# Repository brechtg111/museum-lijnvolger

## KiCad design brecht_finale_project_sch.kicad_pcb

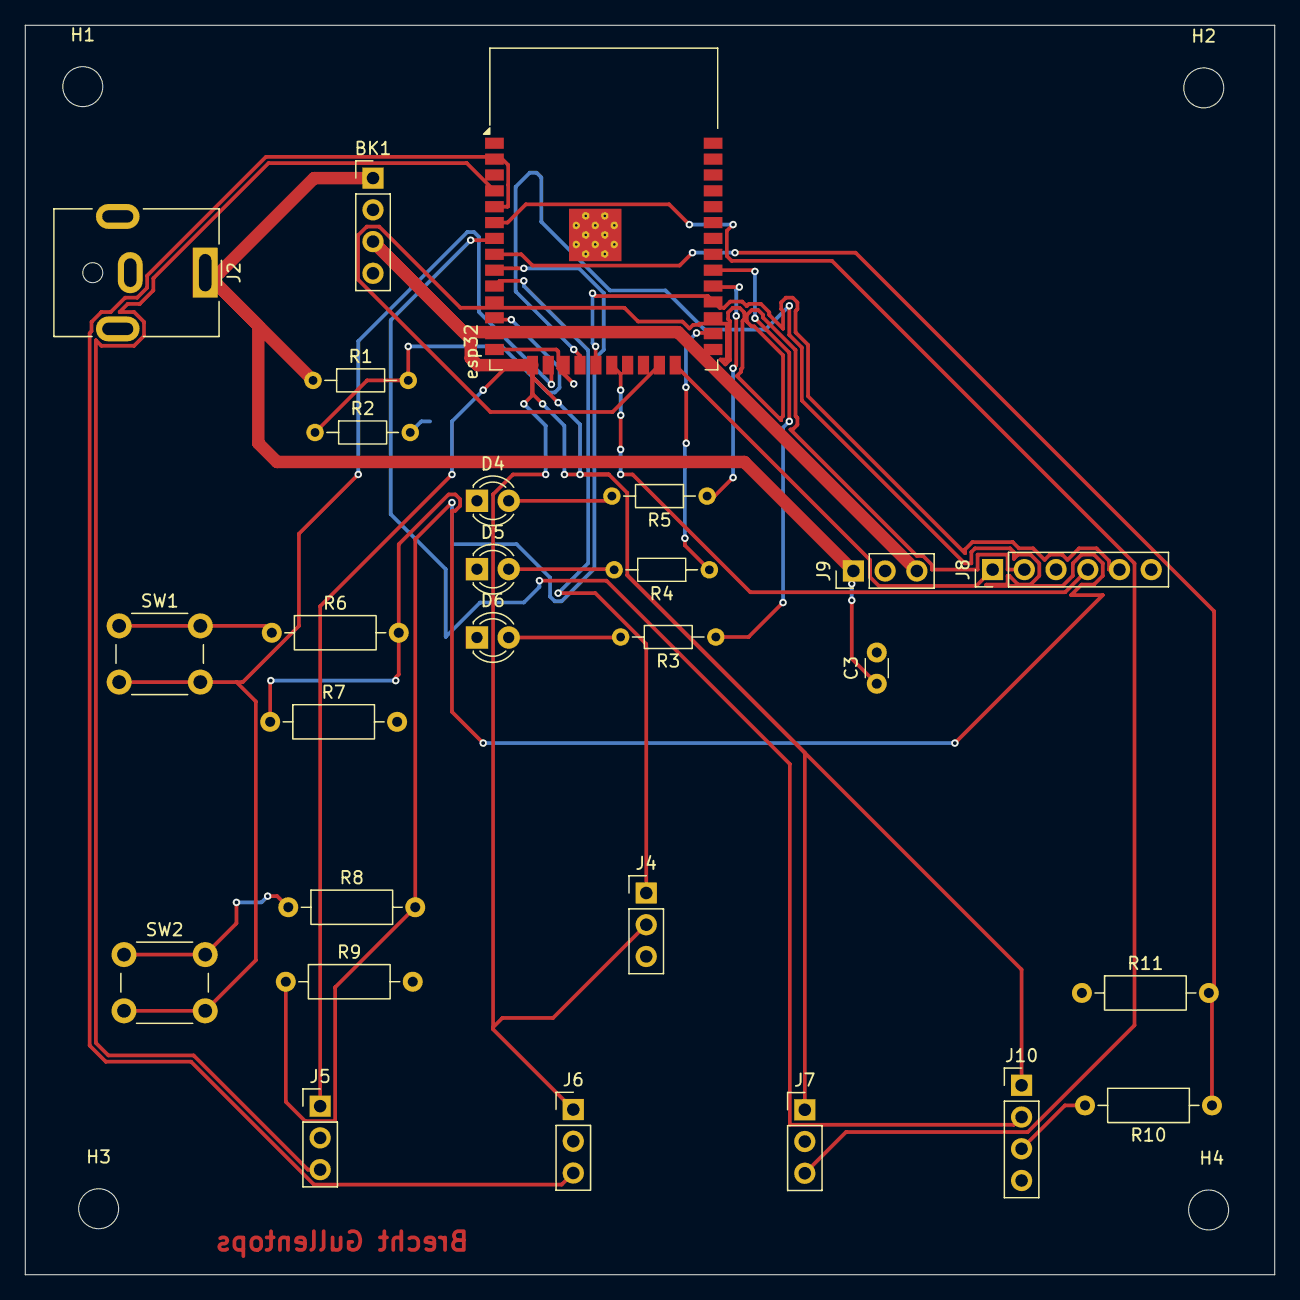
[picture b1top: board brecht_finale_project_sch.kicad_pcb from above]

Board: 2 copper layers, 100.0 x 100.0 mm, 31 parts (0 on the bottom side), 26 nets.

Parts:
BK1: Buck_Mini360; PinHeader_1x04_P2.54mm_Vertical
C3: 1µF; C_Disc_D3.0mm_W1.6mm_P2.50mm
D4, D5, D6: LED; LED_D3.0mm
H1, H2, H3, H4: MountingHole; MountingHole_3.2mm_M3
J2: batterij; BarrelJack_CUI_PJ-063AH_Horizontal
J4: Servo; PinHeader_1x03_P2.54mm_Vertical
J5: IR_S1; PinHeader_1x03_P2.54mm_Vertical
J6: IR_S2; PinHeader_1x03_P2.54mm_Vertical
J7: IR_S3; PinHeader_1x03_P2.54mm_Vertical
J8: L298N_Logic; PinHeader_1x06_P2.54mm_Vertical
J9: L298N_Power; PinHeader_1x03_P2.54mm_Vertical
J10: Sonar1; PinHeader_1x04_P2.54mm_Vertical
R1: 68K; R_Axial_DIN0204_L3.6mm_D1.6mm_P7.62mm_Horizontal
R2: 33K; R_Axial_DIN0204_L3.6mm_D1.6mm_P7.62mm_Horizontal
R3, R4, R5: 220; R_Axial_DIN0204_L3.6mm_D1.6mm_P7.62mm_Horizontal
R6, R8: 1K; R_Axial_DIN0207_L6.3mm_D2.5mm_P10.16mm_Horizontal
R7, R9: 10K; R_Axial_DIN0207_L6.3mm_D2.5mm_P10.16mm_Horizontal
R10: 2K; R_Axial_DIN0207_L6.3mm_D2.5mm_P10.16mm_Horizontal
R11: 3K3; R_Axial_DIN0207_L6.3mm_D2.5mm_P10.16mm_Horizontal
SW1, SW2: SW_Push; SW_PUSH_6mm_H4.3mm
esp32: ESP32-WROOM-32

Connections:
+3.3V: SW1.2, SW2.2, esp32.16 (3V3)
+5V: BK1.3, J4.2, J5.1, J6.1, J7.1, J9.3, J10.1, esp32.15 (VN)
+7.2V: BK1.1, C3.1, J2.1, J9.1, R1.1
GND: BK1.2, BK1.4, C3.2, D4.1 (K), D5.1 (K), D6.1 (K), J2.2, J4.3, J5.2, J6.2, J7.2, J9.2, J10.4, R2.2, R7.2, R9.2, R11.1, esp32.14 (GND), esp32.17 (GND)
IR_Sig1: J5.3, esp32.4 (D34)
IR_Sig2: J6.3, esp32.5 (D35)
IR_Sig3: J7.3, esp32.6 (D32)
M1_1A: J8.1, esp32.24 (D18)
M1_2A: J8.2, esp32.23 (D5)
M2_3A: J8.4, esp32.20 (D4)
M2_4A: J8.5, esp32.19 (D2)
unnamed: D4.2 (A), R5.2
unnamed: D5.2 (A), R4.2
unnamed: D6.2 (A), R3.2
unnamed: J10.3, R10.2
unnamed: R6.1, SW1.1
unnamed: R8.1, SW2.1
unnamed: R4.1, esp32.26 (D21)
unnamed: R5.1, esp32.29 (D22)
unnamed: R3.1, esp32.30 (D23)
START_Signal: R6.2, R7.1, esp32.18 (D15)
STOP_Signal: R8.2, R9.1, esp32.9 (D26)
S_ECHO: R10.1, R11.2, esp32.8 (D25)
S_TRIG: J10.2, esp32.7 (D33)
Servo_SIg: J4.1, esp32.10 (D27)
battery_perc: R1.2, R2.1, esp32.12 (D12)

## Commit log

2026-06-01 Create foto's auto
2026-06-01 Create test
2026-06-01 Create tesdt
2026-06-01 Create files
